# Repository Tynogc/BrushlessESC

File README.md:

# BrushlessESC
ESC für Brushless-Motoren bis 30A

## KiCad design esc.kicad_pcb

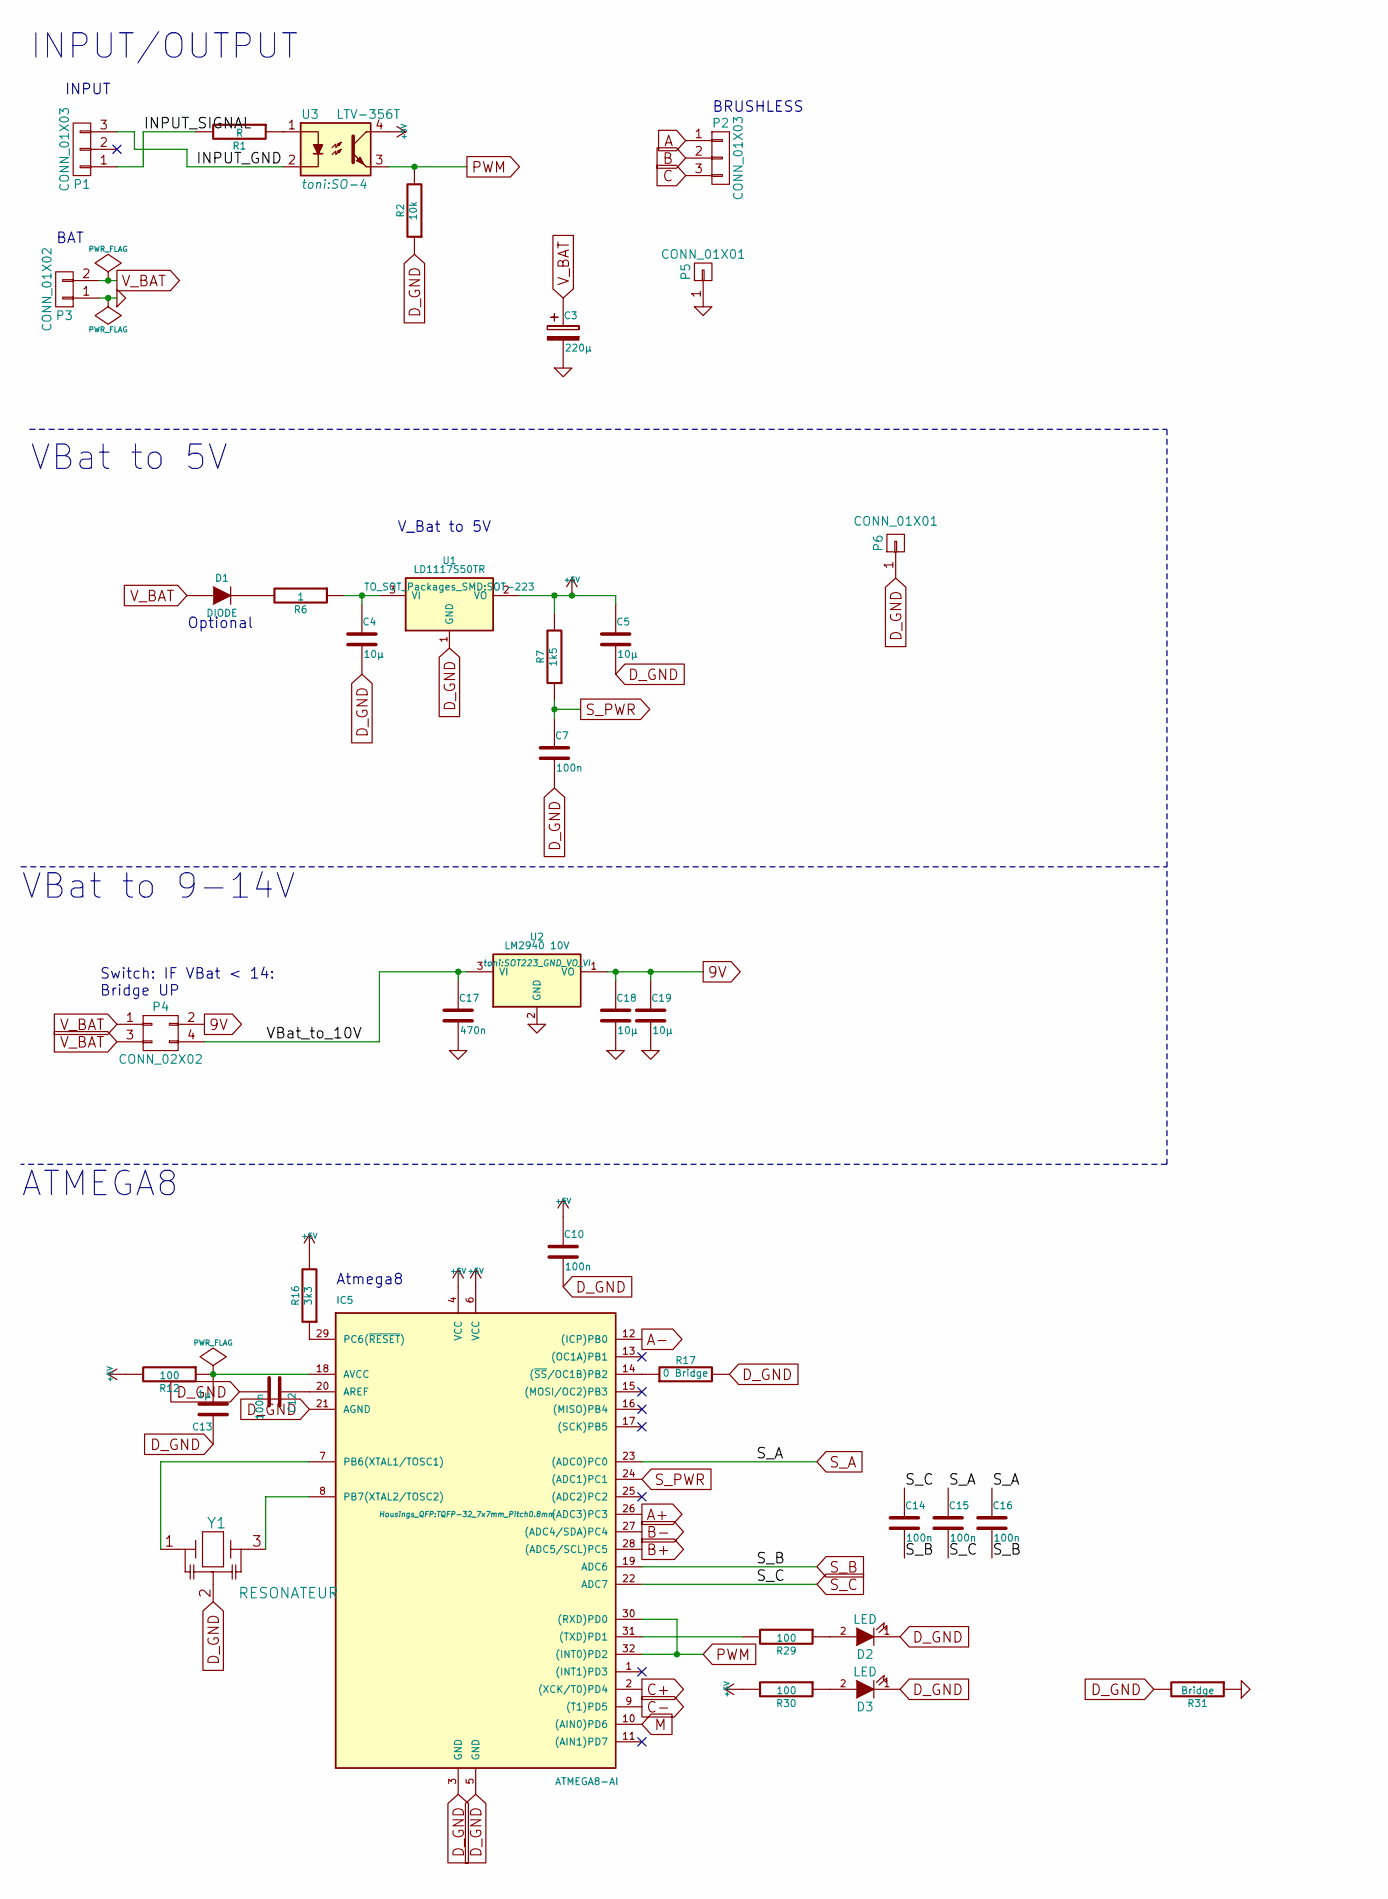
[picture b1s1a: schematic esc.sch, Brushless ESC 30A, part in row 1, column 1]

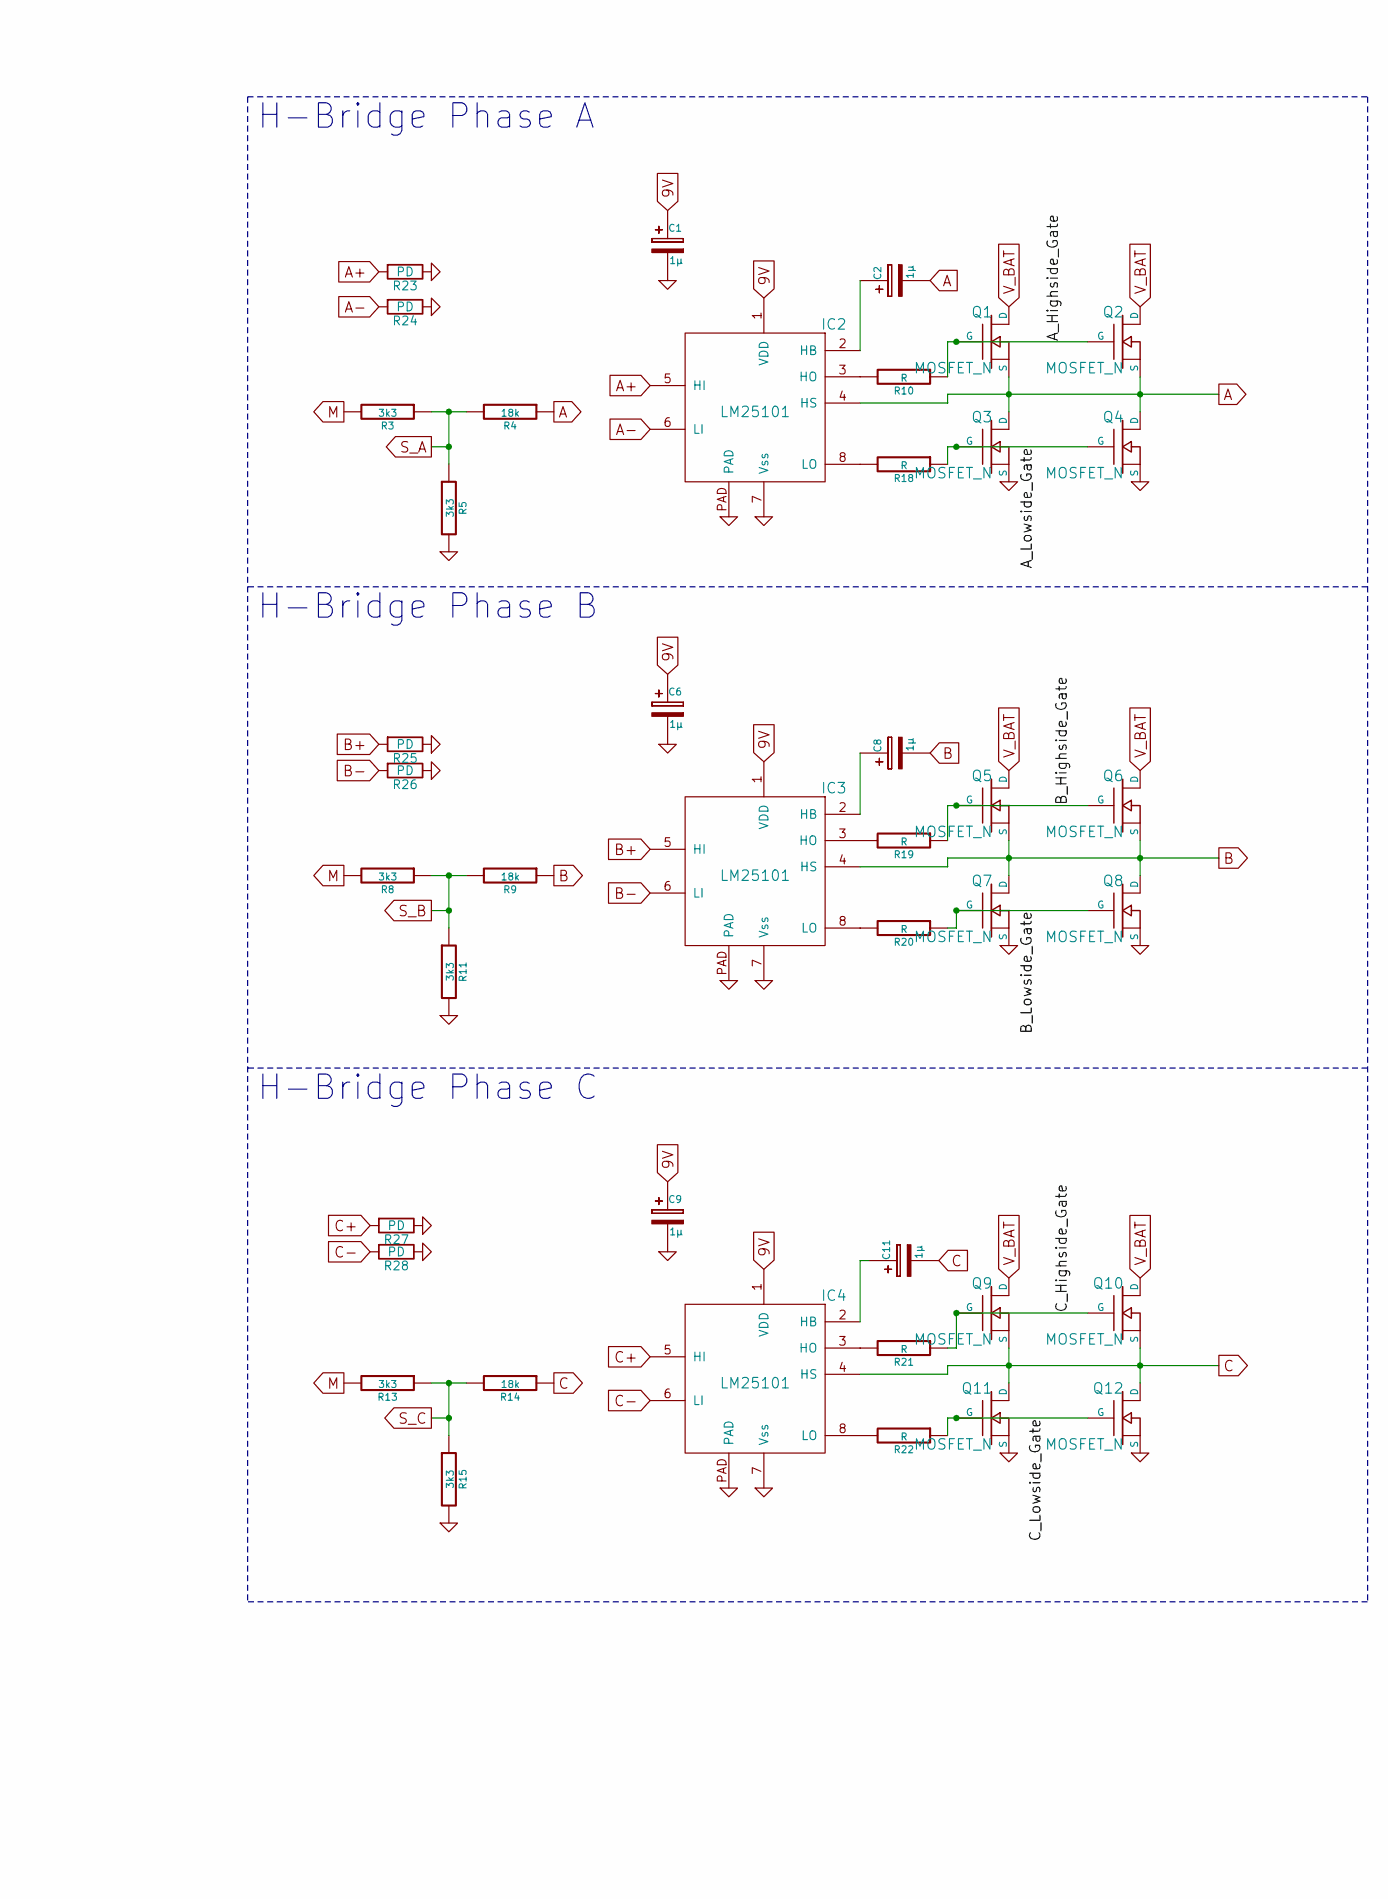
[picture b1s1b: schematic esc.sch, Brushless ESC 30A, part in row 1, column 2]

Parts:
C1, C2, C6, C8, C9, C11, C13: 1µ; C_0805_HandSoldering
C3: 220µ; Elko_vert_11x5mm_RM2_CopperClear
C4, C5, C18, C19: 10µ; C_1206
C7, C10, C12, C14, C15, C16: 100n; C_0603
C17: 470n; C_0805
D1: DIODE; SMA_Handsoldering
D2, D3: LED; LED-0805
IC2, IC3, IC4: LM25101; 8-MSOP
IC5: ATMEGA8-AI; TQFP-32_7x7mm_Pitch0.8mm
P1, P2: CONN_01X03; Socket_Strip_Straight_1x03
P3: CONN_01X02; Socket_Strip_Straight_1x02
P4: CONN_02X02; Socket_Strip_Straight_2x02
P5, P6: CONN_01X01; 1pin
Q1, Q2, Q3, Q4, Q5, Q6, Q7, Q8, Q9, Q10, Q11, Q12: MOSFET_N; SO8_WITH_Heatpipes_New
R1: R; R_0805_HandSoldering
R2: 10k; R_0603
R3, R5, R8, R11, R13, R15, R16: 3k3; R_0603
R4, R9, R14: 18k; R_0603
R6: 1; R_0603
R7: 1k5; R_0603
R10, R18, R19, R20, R21, R22: R; R_0603
R12, R29, R30: 100; R_0603
R17: 0 Bridge; R_0805_HandSoldering
R23, R24, R25, R26, R27, R28: PD; R_0603
R31: Bridge; R_1210_HandSoldering
U1: LD1117S50TR; SOT-223
U2: LM2940 10V; SOT223_GND_VO_VI
U3: LTV-356T; SO-4
Y1: RESONATEUR; CerOsc_3,2x1,3

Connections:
9V: C1.1, C6.1, C9.1, C18.1, C19.1, IC2.1 (VDD), IC3.1 (VDD), IC4.1 (VDD), P4.2, U2.1 (VO)
+5V: C5.1, C10.1, IC5.4 (VCC), IC5.6 (VCC), R7.2, R12.2, R16.2, R30.2, U1.2 (VO), U3.4
/A_Highside_Gate: Q1.G, Q2.G, R10.1
/A_Lowside_Gate: Q3.G, Q4.G, R18.1
/B_Highside_Gate: Q5.G, Q6.G, R19.1
/B_Lowside_Gate: Q7.G, Q8.G, R20.1
/C_Highside_Gate: Q9.G, Q10.G, R21.1
/C_Lowside_Gate: Q11.G, Q12.G, R22.1
/INPUT_GND: P1.3, U3.2
/INPUT_SIGNAL: P1.1, R1.2
/VBat_to_10V: C17.1, P4.4, U2.3 (VI)
A: C2.2, IC2.4 (HS), P2.1, Q1.S, Q2.S, Q3.D, Q4.D, R4.1
A+: IC2.5 (HI), IC5.26 ((ADC3)PC3), R23.2
A-: IC2.6 (LI), IC5.12 ((ICP)PB0), R24.2
B: C8.2, IC3.4 (HS), P2.2, Q5.S, Q6.S, Q7.D, Q8.D, R9.1
B+: IC3.5 (HI), IC5.28 ((ADC5/SCL)PC5), R25.2
B-: IC3.6 (LI), IC5.27 ((ADC4/SDA)PC4), R26.2
C: C11.2, IC4.4 (HS), P2.3, Q9.S, Q10.S, Q11.D, Q12.D, R14.1
C+: IC4.5 (HI), IC5.2 ((XCK/T0)PD4), R27.2
C-: IC4.6 (LI), IC5.9 ((T1)PD5), R28.2
D_GND: C4.2, C5.2, C7.2, C10.2, C12.2, C13.1, D2.1 (K), D3.1 (K), IC5.3 (GND), IC5.5 (GND), IC5.21 (AGND), P6.1, R2.1, R17.2, R31.2, U1.1 (GND), Y1.2
GND: C1.2, C3.2, C6.2, C9.2, C17.2, C18.2, C19.2, IC2.7 (Vss), IC2.PAD, IC3.7 (Vss), IC3.PAD, IC4.7 (Vss), IC4.PAD, P3.1, P5.1, Q3.S, Q4.S, Q7.S, Q8.S, Q11.S, Q12.S, R5.2, R11.2, R15.2, R23.1, R24.1, R25.1, R26.1, R27.1, R28.1, R31.1, U2.2 (GND)
M: IC5.10 ((AIN0)PD6), R3.2, R8.2, R13.2
unnamed: C2.1, IC2.2 (HB)
unnamed: C4.1, R6.1, U1.3 (VI)
unnamed: C8.1, IC3.2 (HB)
unnamed: C11.1, IC4.2 (HB)
unnamed: C12.1, IC5.20 (AREF)
unnamed: C13.2, IC5.18 (AVCC), R12.1
unnamed: D1.2 (K), R6.2
unnamed: D2.2 (A), R29.1
unnamed: D3.2 (A), R30.1
unnamed: IC2.3 (HO), R10.2
unnamed: IC2.8 (LO), R18.2
unnamed: IC3.3 (HO), R19.2
unnamed: IC3.8 (LO), R20.2
unnamed: IC4.3 (HO), R21.2
unnamed: IC4.8 (LO), R22.2
unnamed: IC5.7 (PB6(XTAL1/TOSC1)), Y1.1
unnamed: IC5.8 (PB7(XTAL2/TOSC2)), Y1.3
unnamed: IC5.14 ((~SS~/OC1B)PB2), R17.1
unnamed: IC5.29 (PC6(~RESET~)), R16.1
unnamed: IC5.31 ((TXD)PD1), R29.2
unnamed: R1.1, U3.1
PWM: IC5.30 ((RXD)PD0), IC5.32 ((INT0)PD2), R2.2, U3.3
S_A: C15.1, C16.1, IC5.23 ((ADC0)PC0), R3.1, R4.2, R5.1
S_B: C14.2, C16.2, IC5.19 (ADC6), R8.1, R9.2, R11.1
S_C: C14.1, C15.2, IC5.22 (ADC7), R13.1, R14.2, R15.1
S_PWR: C7.1, IC5.24 ((ADC1)PC1), R7.1
V_BAT: C3.1, D1.1 (A), P3.2, P4.1, P4.3, Q1.D, Q2.D, Q5.D, Q6.D, Q9.D, Q10.D

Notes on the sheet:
Atmega8
BRUSHLESS
INPUT
BAT
V_Bat to 5V
Switch: IF VBat < 14: Bridge UP
H-Bridge Phase A
H-Bridge Phase B
H-Bridge Phase C
INPUT/OUTPUT
VBat to 5V
ATMEGA8
VBat to 9-14V
Optional

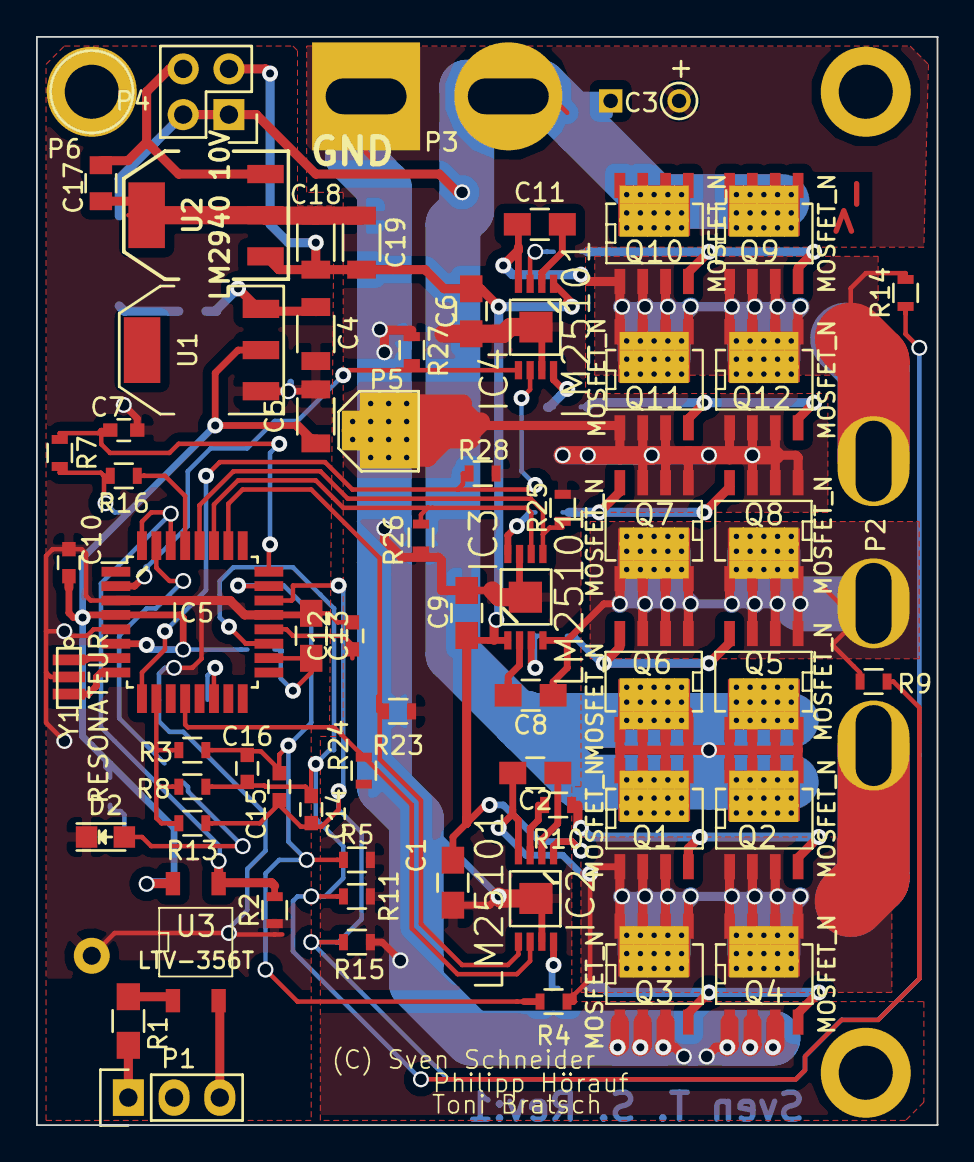
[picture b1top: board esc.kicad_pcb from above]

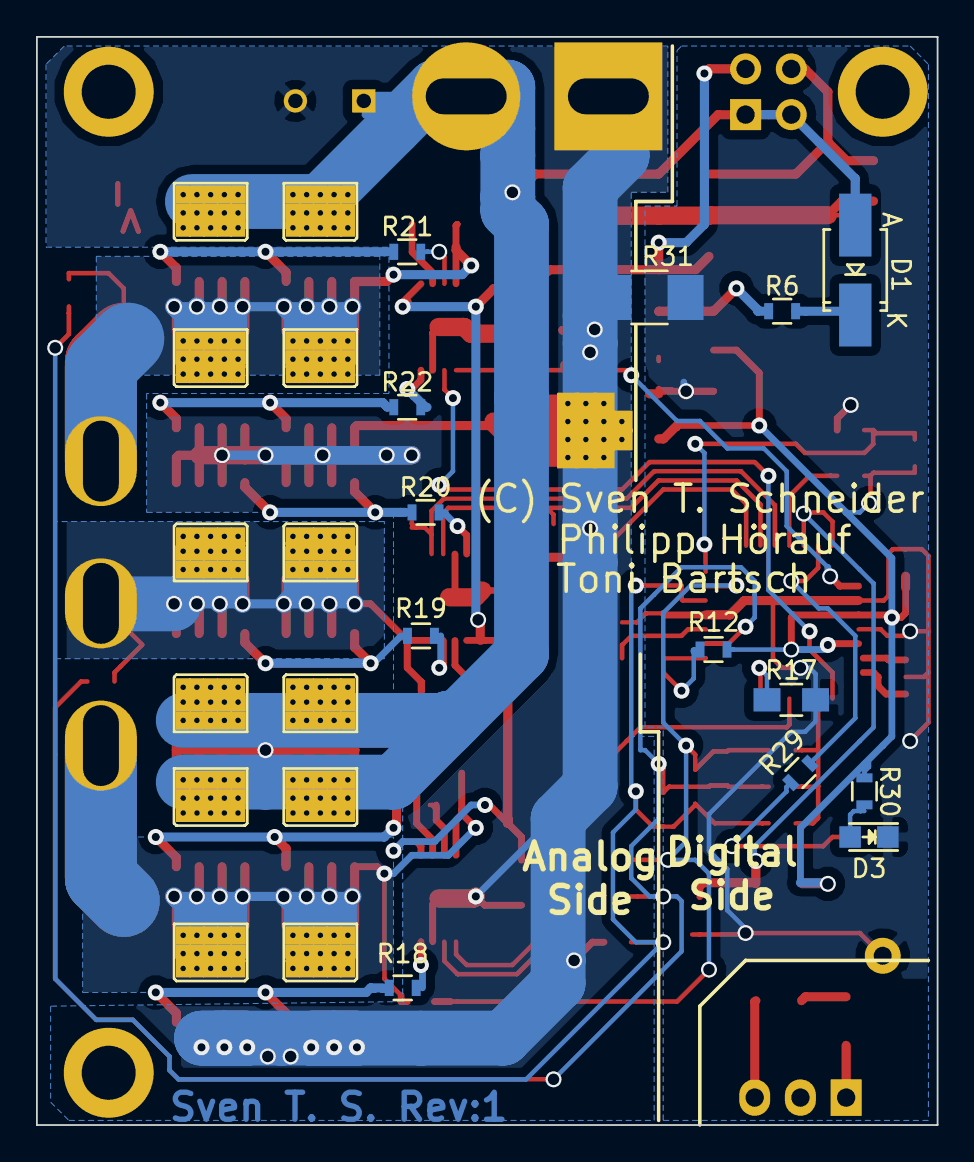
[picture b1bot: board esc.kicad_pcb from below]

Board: 2 copper layers, 50.0 x 60.5 mm, 79 parts (13 on the bottom side), 50 nets.

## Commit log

2015-11-13 Initialisierung
2015-11-13 Added PWR flag
2015-11-13 Create Mosfets_And_Drivers
2015-11-15 Update Mosfets_And_Drivers
2015-11-16 Plan quasi fertig
2015-11-16 Layout done!
2015-11-16 Platiene begonnen
2015-11-17 Netlist and PCB started
2015-11-17 PCB works...
2015-11-17 PCB weiter+Layout R
2015-11-18 PCB almost done!
2015-11-18 PCB V1.0
2015-11-18 Added pull down Resistors
2015-11-20 Reduced part count, Splittet 22uF cap C17 into two 10uF
2015-11-20 Added suport for Anderson PowerPole as input connectors.
2015-11-23 Langloch fuer Power-Pole-Kontackte
2015-11-23 Langlöcher für ausgang
2015-11-23 PWR-on LED und Fault-LED eingefügt
2015-11-24 FET-Pins sind jetzt auf Solid umgestellt
2015-11-24 Optokoppler zu LTV-356T weil muss so
2015-11-24 Optokoppler geändert
2015-11-25 Getrennte Masse für Digital-Teil
2015-11-30 Spannungswandler U1 geändert auf LD1117
2015-12-04 Kondensator C3 geändert (Auf richtigen Footprint) + Bestückungsdruck
2015-12-04 Gerber erzeugt
2015-12-08 Versionierung geändert
